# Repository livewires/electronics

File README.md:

# LiveWires Electronics Repo

Welcome to the LiveWires electronics repo. Eventually hopefully all the project information will be on here. For now it's just the new projects since this has been created.

Worksheets can be downloaded by finding the latest release (check the right hand bar on github) and downloading the worksheets.zip file

## Macro Pad

This is the LiveWires Macro Pad, an 8-key macro pad based on a Raspberry Pi Pico and cherry switches. It has up to 16 configurable pages of keys, and runs CircuitPython.

[Click here to find out more](macropad/README.md)

## Analogue Synthesiser

This is the LiveWires analogue synthesiser, a musical instrument with 5 octaves of output, a 1 octave keyboard, 8 control dials and entirely analogue processing of a digitally produced wave.

[Click here to find out more](synth/README.md)

## 3D LED Cube

The LiveWires LED cube, a 3x3x3 grid of LEDs with custom animations. 

[Click here to find out more](led-cube/README.md)

## Release Process

Create a draft release by going to `Releases > Draft a new release` in github.

Set the title accordingly, and change the "Tag" to create a new tag, vX.Y, where X.Y must be larger than the previous release. Describe the reason for doing the release in the description.

Download the worksheets.zip artifact from a build run with the desired changes, and upload them to the release. If no build has been performed in the last 90 days, you will need to manually trigger a new build. Go to the actions page, click on the action on the left hand side titled "Build LaTeX Documents" and then click the "Run Workflow" button

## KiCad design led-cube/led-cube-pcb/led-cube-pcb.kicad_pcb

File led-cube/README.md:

# LiveWires LED Cube

A 3x3x3 cube with completely programmable animations using the [animator](http://livewires.org.uk/led-cube)

## Own an LED cube? Start here!

Well done for building your LED cube! Here's where you can find all the information about it.

## How it works

The cube has 27 LEDs arranged in a 3×3×3 grid. Rather than wiring each LED individually, they share connections by layer — only one layer is switched on at a time, but they cycle through fast enough (~98 times per second) that all three appear lit at once.

This cycling is handled by the Pico's PIO hardware, which runs independently in the background so Python doesn't have to worry about the timing. Python's only job is to advance through the animation frames at the right speed and update which LEDs should be on.

Animations are loaded from `animations.json`. Each animation has a list of frames and a framerate. Pressing the button on GP16 skips to the next animation.

### Putting your own animations on

Use our [animation tool](http://livewires.org.uk/led-cube)! You can load the existing animations from the cube using the "Load JSON" button at the bottom. All you need to do is plug the pico in over USB and it'll appear as a removable drive. 

Once you're ready to try your animations on the cube, press "Download JSON" and move the `animations.json` file to the pico. Note, it must be named exactly that, if you've got several copies (e.g. `animations (1).json`) you'll have to rename it on the device. 

### Troubleshooting

That should be all you need. If you get stuck, feel free to get in touch with a leader, or post an issue here on github. 

If you've bricked your cube by changing something, don't worry, it should be easy to fix. Just download the contents of the "code" folder in github and copy it across to the device. 

## Setting up for the camp?

This should only need to be done by the leader running the sessions on the camp. This is what needs doing in advance:

* PCB needs ordering
* Components need kitting
* Pico needs soldering
* Pico needs initial software installing
* Jig needs making

#### PCB 

At the minute, this is a non-etch project. The PCB is ordered from JLCPCB or a similar service using the gerber files. These can be found in the version's output folder (e.g. [here](led-cube-pcb/releases/lw-led-cube_1.0/lw-led-cube_1.0_Gerbers.zip)).

These will take a few weeks to arrive so needs doing in plenty of time!

#### Components

Components list is in the BOM. For example, the revision 1 BOM can be found at [macropad-rev1/output/macropad-rev1-BOM.ods](led-cube-pcb/releases/lw-led-cube_1.0/full-project-bom_1.0.ods). 

#### Soldering the Pico

To save money, we're ordering the Pi Pico un-soldered. This means a leader will have to solder the two 20-pin headers to the Pico. They should protrude from the bottom of the Pico (i.e. the side with no components on), so the solder goes on the top of the board (i.e. the side _with_ the components on). 

#### Setting up the Pico

CircuitPython needs installing on the Pico, and then our code needs copying. The version used for development was 10.2.1, which is [copied into this repo](adafruit-circuitpython-raspberry_pi_pico-en_GB-10.2.1.uf2). 

You should now be able to copy the contents of the [code](code) folder onto the new CIRCUITPY drive. 

##### 1. Flash CircuitPython

Hold the **BOOTSEL** button on the Pico, plug it into USB, then release BOOTSEL.  
The Pico will appear as a USB drive called **RPI-RP2**.

Copy the firmware onto that drive:

```
adafruit-circuitpython-raspberry_pi_pico-en_GB-10.2.1.uf2  →  RPI-RP2
```

The Pico will reboot automatically and reappear as **CIRCUITPY**.

##### 2. Copy the code

Copy the contents of the `code/` folder to the root of the CIRCUITPY drive:

```
code/
├── code.py           →  CIRCUITPY/code.py
├── animations.json   →  CIRCUITPY/animations.json
└── lib/
    └── adafruit_pioasm.mpy  →  CIRCUITPY/lib/adafruit_pioasm.mpy
```

The Pico will run `code.py` automatically as soon as the files are in place.

#### Making a Jig

Soldering the pico headers to the PCB is much easier for the YP if they can physically join both 20-pin connectors together, the right distance apart. This can be done by attaching the connectors to a Pico before soldering them, but this risks breaking the Pico. So a jig can be made using header pins and a bit of veroboard. 

Use a Pico to copy the exact spacing of the pins. It should look something like this:

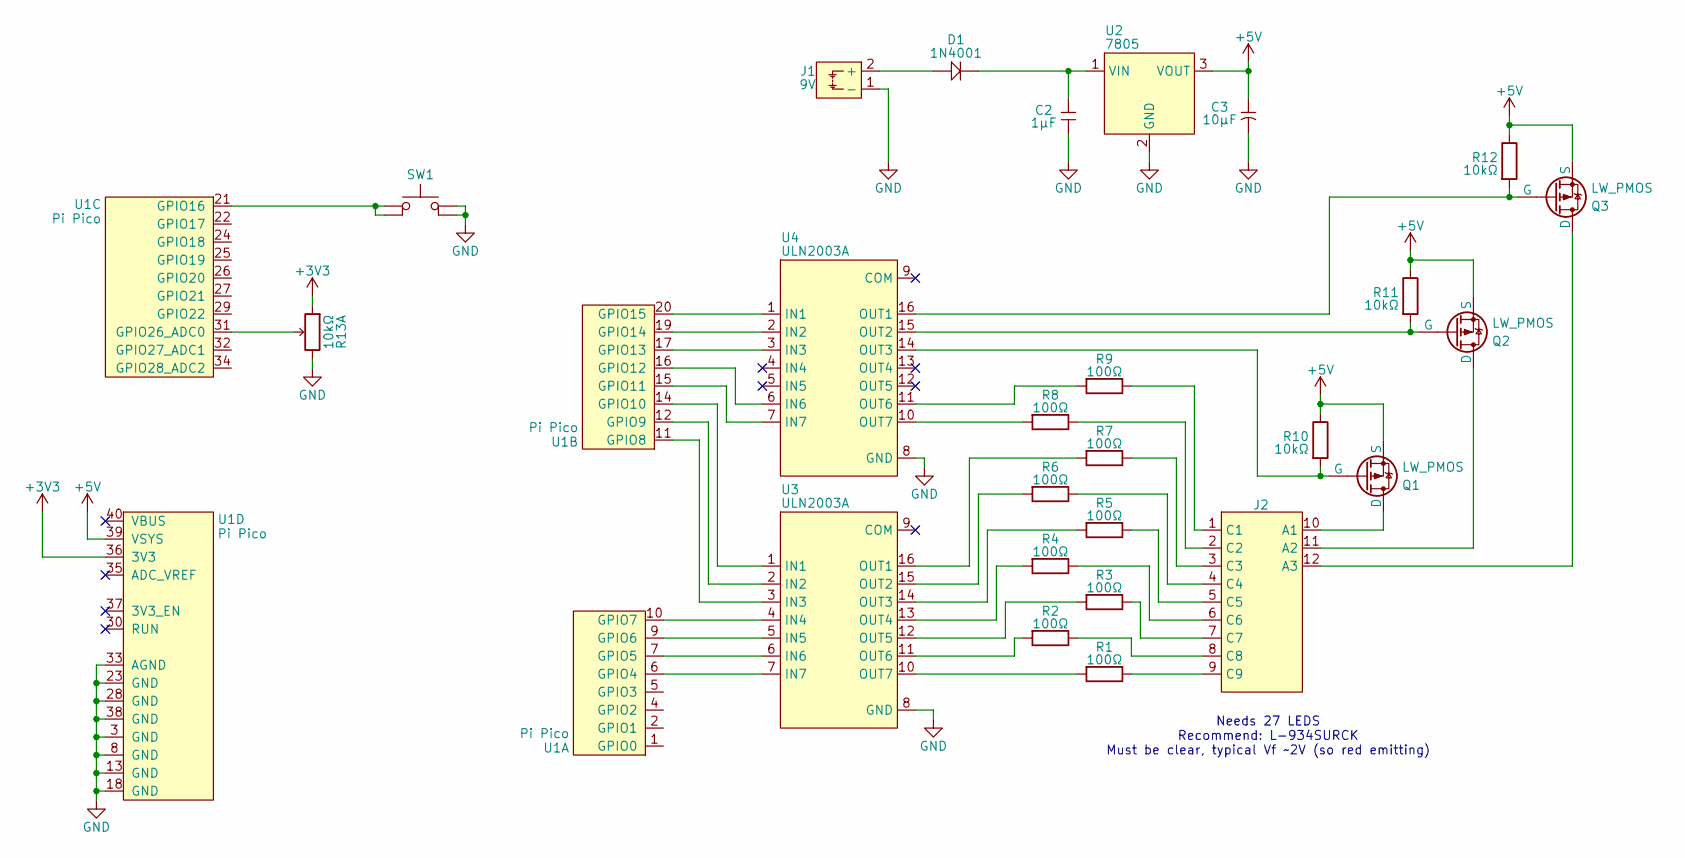
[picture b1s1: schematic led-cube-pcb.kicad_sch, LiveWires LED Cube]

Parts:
C2: 1µF; LW_CeramicCap_5.08mm; MPN TS170R1H105MSBFB0R
C3: 10µF; LW_CAP_Radial_D5.0mm_P2.00mm; MPN TS13DE1E100MSB030R
D1: 1N4001; LW_DIODE; MPN 1N4001
J1: 9V; LW_BATTERY_HOLDER; MPN 9V-I-Clip
J2: LED Cube; LW_LEDCUBE
Q1, Q2, Q3: LW_PMOS; LW_TO-92; MPN ZVP2110A
R1, R2, R3, R4, R5, R6, R7, R8, R9: 100Ω; LW_Res; MPN MF0W4FF1000
R10, R11, R12: 10kΩ; LW_Res; MPN MF0W4FF1002
R13: 10kΩ; PTV112-4420A; MPN PTV112-4420A-A103
SW1: LW_Tactile_Switch; LW_TACTILE_SW; MPN 783862
U1: Pi Pico; LW_RPi_Pico_SMD_TH; MPN SC0915
U2: 7805; TO-220-3_Vertical; MPN L7805
U3, U4: ULN2003A; DIP-16_W7.62mm_Socket; MPN ULN2003A

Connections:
+3V3: R13.2 (L), U1.36 (3V3)
+5V: C3.1, Q1.1 (S), Q2.1 (S), Q3.1 (S), R10.2, R11.2, R12.2, U1.39 (VSYS), U2.3 (VOUT)
GND: C2.1, C3.2, J1.1 (-), R13.6 (R), SW1.3, SW1.4, U1.3 (GND), U1.8 (GND), U1.13 (GND), U1.18 (GND), U1.23 (GND), U1.28 (GND), U1.33 (AGND), U1.38 (GND), U2.2 (GND), U3.8 (GND), U4.8 (GND)
unnamed: D1.A, J1.2 (+)
unnamed: J2.10 (A1), Q1.3 (D)
unnamed: J2.11 (A2), Q2.3 (D)
unnamed: J2.12 (A3), Q3.3 (D)
unnamed: J2.1 (C1), R9.2
unnamed: J2.2 (C2), R8.2
unnamed: J2.3 (C3), R7.2
unnamed: J2.4 (C4), R6.2
unnamed: J2.5 (C5), R5.2
unnamed: J2.6 (C6), R4.2
unnamed: J2.7 (C7), R3.2
unnamed: J2.8 (C8), R2.2
unnamed: J2.9 (C9), R1.2
unnamed: Q1.2 (G), R10.1, U4.14 (OUT3)
unnamed: Q2.2 (G), R11.1, U4.15 (OUT2)
unnamed: Q3.2 (G), R12.1, U4.16 (OUT1)
unnamed: R13.1 (C), U1.31 (GPIO26_ADC0)
unnamed: U1.6 (GPIO4), U3.7 (IN7)
unnamed: U1.7 (GPIO5), U3.6 (IN6)
unnamed: U1.9 (GPIO6), U3.5 (IN5)
unnamed: U1.10 (GPIO7), U3.4 (IN4)
unnamed: U1.11 (GPIO8), U3.3 (IN3)
unnamed: U1.12 (GPIO9), U3.2 (IN2)
unnamed: U1.14 (GPIO10), U3.1 (IN1)
unnamed: U1.15 (GPIO11), U4.7 (IN7)
unnamed: U1.16 (GPIO12), U4.6 (IN6)
unnamed: U1.17 (GPIO13), U4.3 (IN3)
unnamed: U1.19 (GPIO14), U4.2 (IN2)
unnamed: U1.20 (GPIO15), U4.1 (IN1)
unnamed: SW1.1, SW1.2, U1.21 (GPIO16)
unnamed: C2.2, D1.K, U2.1 (VIN)
unnamed: R7.1, U3.16 (OUT1)
unnamed: R6.1, U3.15 (OUT2)
unnamed: R5.1, U3.14 (OUT3)
unnamed: R4.1, U3.13 (OUT4)
unnamed: R3.1, U3.12 (OUT5)
unnamed: R2.1, U3.11 (OUT6)
unnamed: R1.1, U3.10 (OUT7)
unnamed: R9.1, U4.11 (OUT6)
unnamed: R8.1, U4.10 (OUT7)

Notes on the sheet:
Needs 27 LEDS Recommend: L-934SURCK Must be clear, typical Vf ~2V (so red emitting)

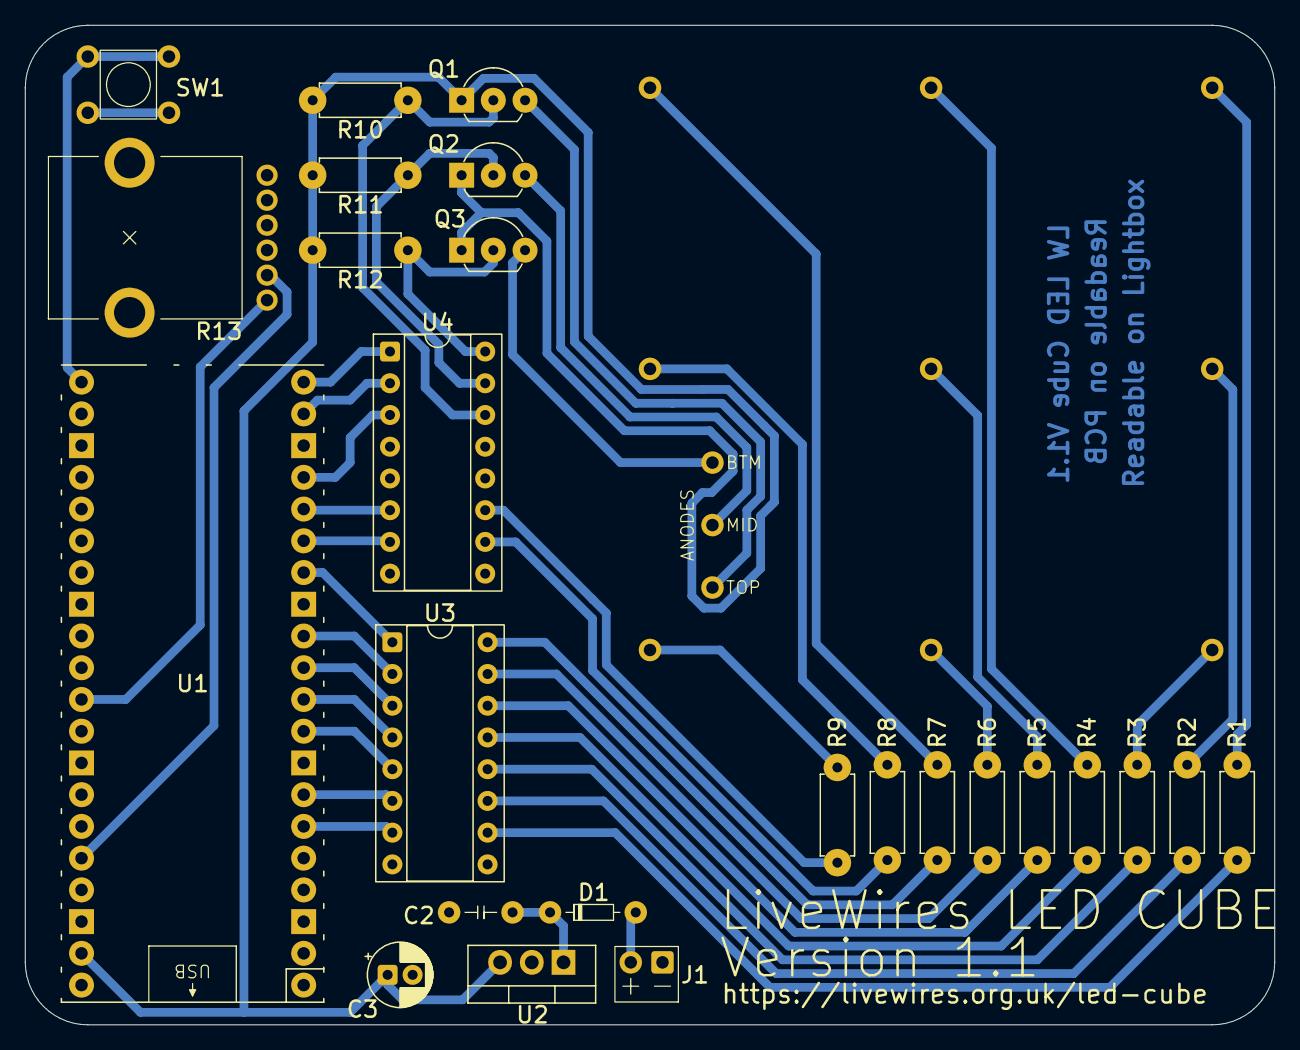
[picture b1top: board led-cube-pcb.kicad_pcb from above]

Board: 2 copper layers, 100.0 x 80.0 mm, 26 parts (0 on the bottom side), 43 nets.

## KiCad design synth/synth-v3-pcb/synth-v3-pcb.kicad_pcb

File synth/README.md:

# LiveWires Analogue Synthesiser

## Specification

 * Total range: 5 octaves (C1 to C6)
 * Keyboard: 1 octave capacitive touch keyboard
 * Wave generator: Sine wave
 * Low Frequency Oscillator (LFO) to control volume
 * Attack and Release envelopes
 * Overdrive for distortion
 * Low Pass Filter (LPF) with cutoff and resonance control
 * 3.5mm jack output for headphones

## Pictures

## How it works

13 capacitive touch keys (plus an additional two control buttons) are read by the pi pico. The pico generates a sine wave and outputs it using Pulse Width Modulation (PWM) to simulate an analogue output (since the pico doesn't come equipped with a DAC onboard). This signal is low-pass-filtered using a 2nd order RC filter, which makes it more closely approximate a sine wave.

An LFO generates a low-frequency (~0.05 - 5Hz) triangle wave. The Pico also outputs a digital signal that indicates whether a key is pressed, which is filtered by the Attack-Release (AR) circuitry. 

The voltage controlled amplifier (VCA) amplifies the sine wave by the control signal, which is the combination of the LFO and AR outputs.

The VCA output is then fed through the Low Pass Filter. 

## Setting up for the camp?

This should only need to be done by the leader running the sessions on the camp. This is what needs doing in advance:

* PCB needs ordering
* Components need kitting
* Pico needs soldering
* Pico needs software installing

#### PCB 

This is a non-etch project. The PCB is ordered from JLCPCB or a similar service using the gerber files. These can be found in the version's output folder (in [here](synth-v3-pcb/releases/)). Look for `*-gerbers.zip`. 

> [!IMPORTANT]
> These will take a few weeks to arrive so needs doing in plenty of time!

The JLCPCB ordering details are as follows:
* Basic Info
  * Base material: FR4
  * Layers: 2
  * Dimensions: [Automatic based on PCB gerbers]
  * Product type: Industrial/Consumer Electronics
* PCB Specification
  * Different Design: 1
  * Delivery Format: Single PCB
  * PCB Thicknes: 1.6mm
  * PCB Color: Black
  * Silkscreen: White
  * Material type: <doesn't matter, cheapest>
  * Surface finish: "LeadFree HASL" or "ENIG"
* High-Spec Options
  * Outer copper weight: 1oz
  * Via covering: Tented
  * Via plating method: Not specified
  * Min via hole size/diameter: 0.3mm <largest and therefore cheapest minimum at time of writing. Actual via diameter in board design is 0.35mm>
  
All other options set to cheapest option, usually defaults

### Components

Components list is in the BOM. For example, the revision 3.1 BOM can be found at [synth-v3-pcb/releases/lw-synth-v3.1/full-project-bom_rev_3.1.ods](synth-v3-pcb/releases/lw-synth-v3.1/full-project-bom_rev_3.1.ods). 

Knobs can be ordered for this project, but if available, 3D printed ones are easier and cheaper. The files for this can be found in `electronics/components/knobs`. If you are ordering some, be aware that some knobs you can order don't have the correct orientation of the ident in relation to the D of the potentiometer shaft. 

### Soldering the Pico

To save money, we're ordering the Pi Pico un-soldered. This means a leader will have to solder the two 20-pin headers to the Pico. They should protrude from the bottom of the Pico (i.e. the side with no components on), so the solder goes on the top of the board (i.e. the side _with_ the components on). 

#### Making a Jig

See the readme for the macropad project.

### Setting up the Pico's software

The software for the pico is written in C (not micropython, like the macropad). This means you simply need to copy [lw-synth.uf2](lw-synth.uf2) to the Pico's drive.

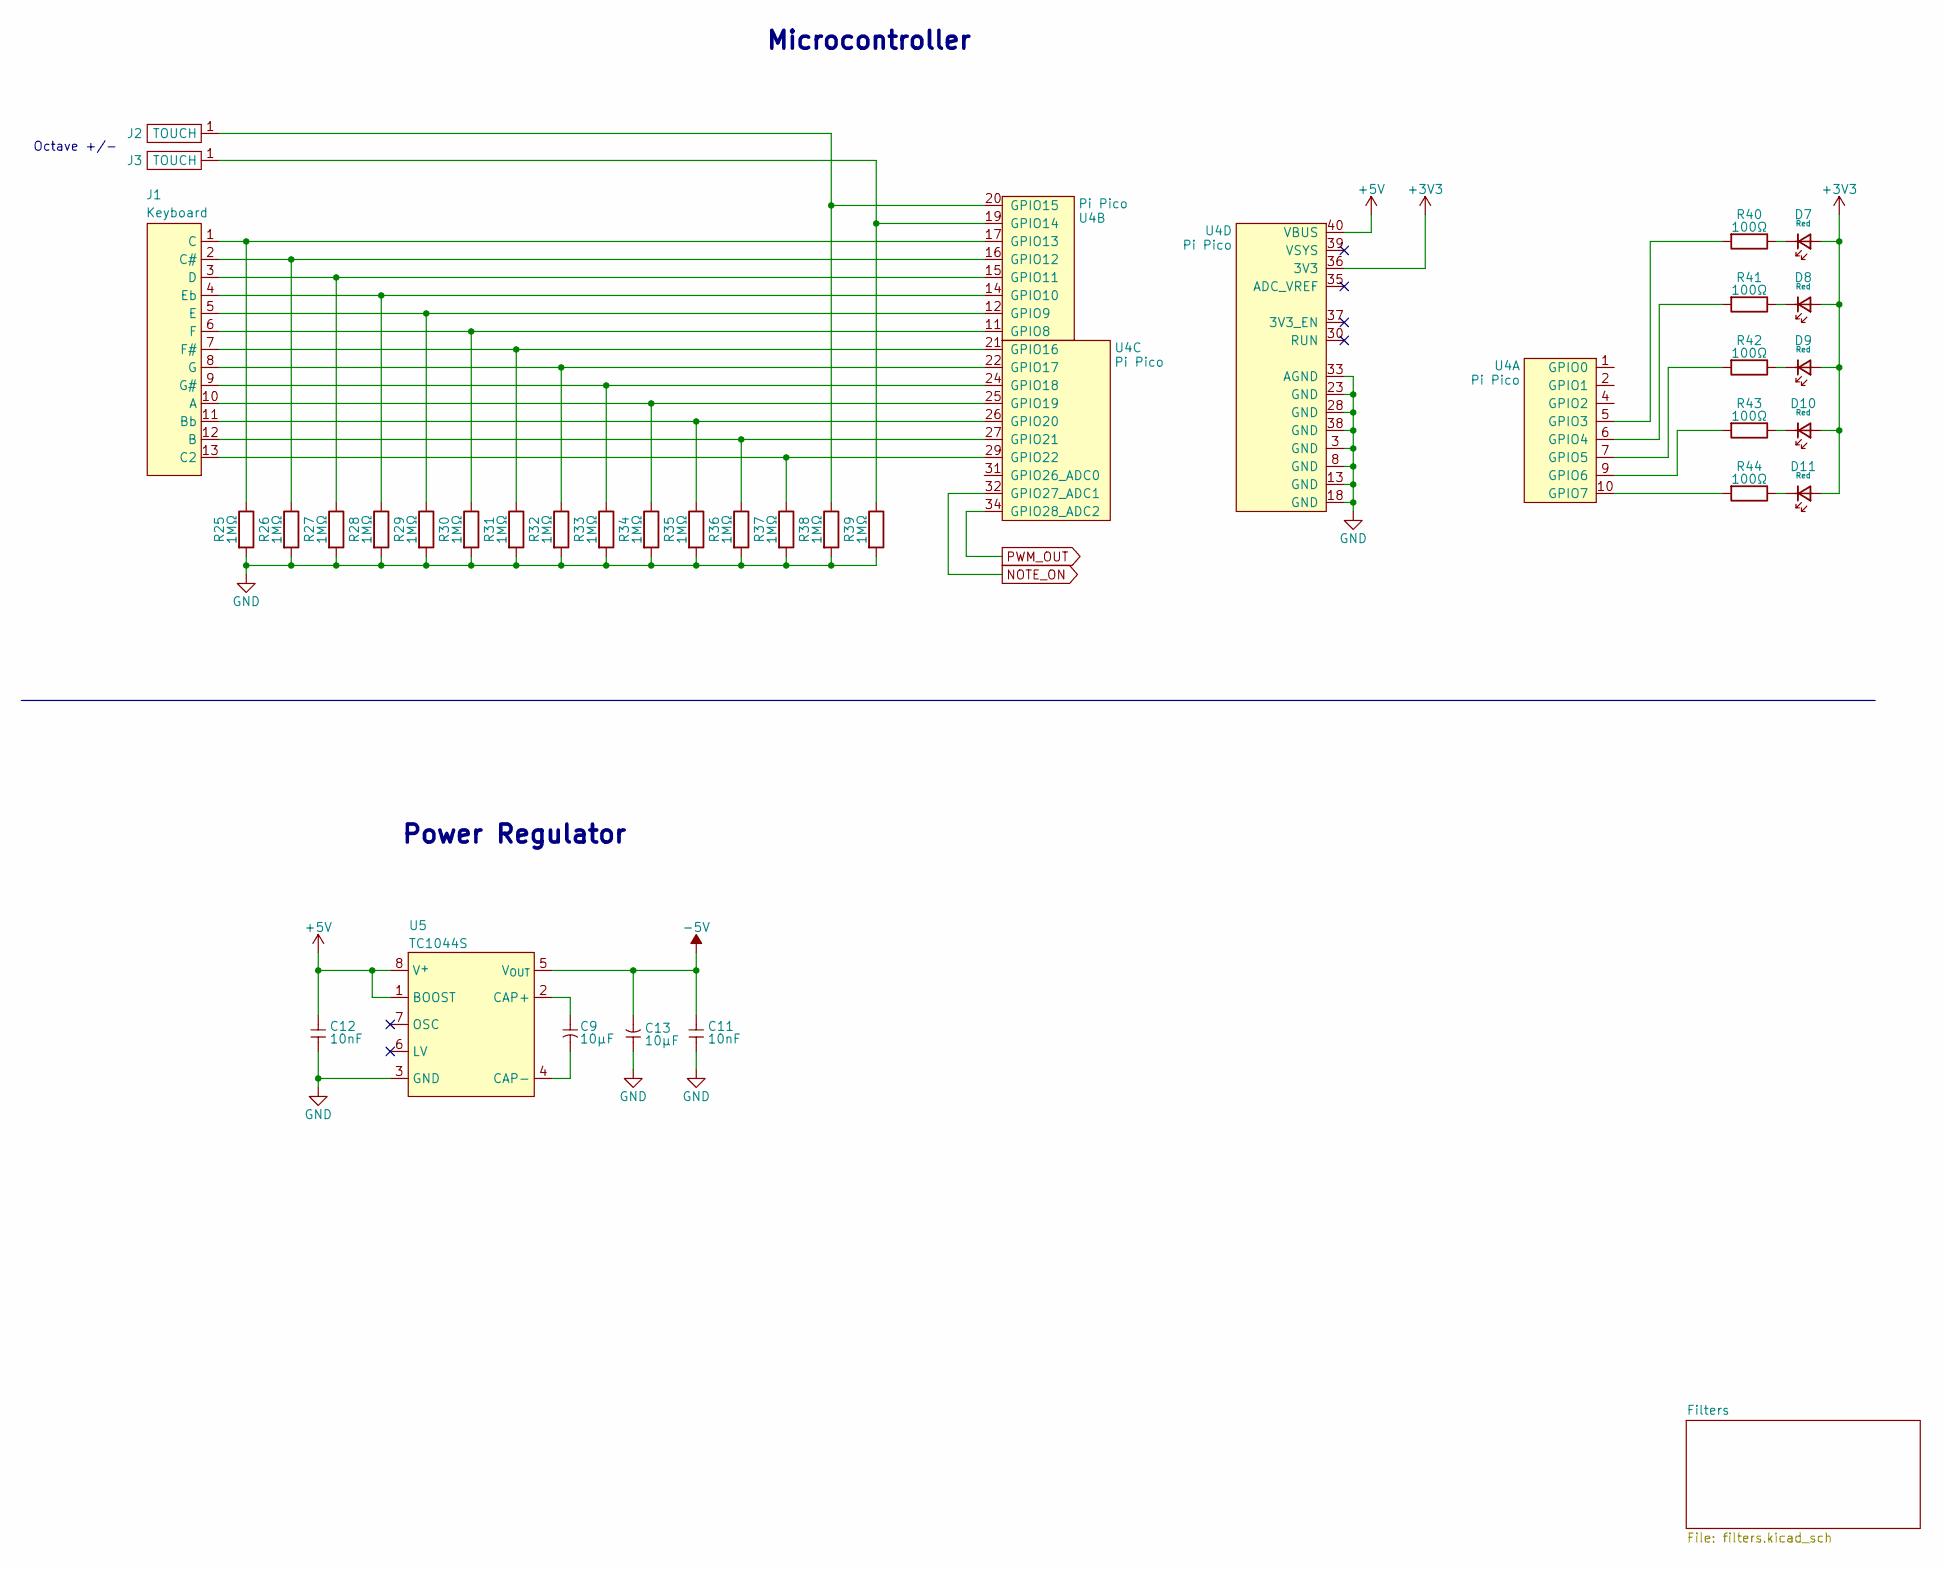
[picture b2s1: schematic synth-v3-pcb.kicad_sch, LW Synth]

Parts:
C9, C13: 10µF; LW_CAP_Radial_D5.0mm_P2.00mm; MPN TS13DE1E100MSB030R
C11, C12: 10nF; LW_CeramicCap_5.08mm; MPN TS170R1H103MSBFB0R
D7, D8, D9, D10, D11: Red; LW_LED_D5.0mm; MPN 1573708
J1: Keyboard; LW_PIANO
J2, J3: 15mm Touch; BASIC_TOUCH_PAD_15mm
R25, R26, R27, R28, R29, R30, R31, R32, R33, R34, R35, R36, R37, R38, R39: 1MΩ; LW_Res; MPN MF0W4FF1004
R40, R41, R42, R43, R44: 100Ω; LW_Res; MPN MF0W4FF1000
U4: Pi Pico; LW_RPi_Pico_SMD_TH; MPN SC0915
U5: TC1044S; LW_DIP8; MPN TC1044SCPA

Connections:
+3V3: D7.A, D8.A, D9.A, D10.A, D11.A, U4.36 (3V3)
+5V: C12.2, U4.40 (VBUS), U5.1 (BOOST), U5.8 (V^{+}); also elsewhere on the board
-5V: C11.2, C13.2, U5.5 (V_{OUT}); also elsewhere on the board
GND: C11.1, C12.1, C13.1, R25.1, R26.1, R27.1, R28.1, R29.1, R30.1, R31.1, R32.1, R33.1, R34.1, R35.1, R36.1, R37.1, R38.1, R39.1, U4.3 (GND), U4.8 (GND), U4.13 (GND), U4.18 (GND), U4.23 (GND), U4.28 (GND), U4.33 (AGND), U4.38 (GND), U5.3 (GND); also elsewhere on the board
NOTE_ON: U4.32 (GPIO27_ADC1); also elsewhere on the board
unnamed: D7.K, R40.2
unnamed: D8.K, R41.2
unnamed: D9.K, R42.2
unnamed: D10.K, R43.2
unnamed: D11.K, R44.2
unnamed: J1.10 (A), R34.2, U4.25 (GPIO19)
unnamed: J1.12 (B), R36.2, U4.27 (GPIO21)
unnamed: J1.11 (Bb), R35.2, U4.26 (GPIO20)
unnamed: J1.13 (C2), R37.2, U4.29 (GPIO22)
unnamed: J1.2 (C#), R26.2, U4.16 (GPIO12)
unnamed: J1.1 (C), R25.2, U4.17 (GPIO13)
unnamed: J1.3 (D), R27.2, U4.15 (GPIO11)
unnamed: J1.5 (E), R29.2, U4.12 (GPIO9)
unnamed: J1.4 (Eb), R28.2, U4.14 (GPIO10)
unnamed: J1.7 (F#), R31.2, U4.21 (GPIO16)
unnamed: J1.6 (F), R30.2, U4.11 (GPIO8)
unnamed: J1.9 (G#), R33.2, U4.24 (GPIO18)
unnamed: J1.8 (G), R32.2, U4.22 (GPIO17)
unnamed: J2.1 (TOUCH), R38.2, U4.20 (GPIO15)
unnamed: J3.1 (TOUCH), R39.2, U4.19 (GPIO14)
unnamed: R40.1, U4.5 (GPIO3)
unnamed: R41.1, U4.6 (GPIO4)
unnamed: R42.1, U4.7 (GPIO5)
unnamed: R43.1, U4.9 (GPIO6)
unnamed: R44.1, U4.10 (GPIO7)
unnamed: C9.1, U5.2 (CAP+)
unnamed: C9.2, U5.4 (CAP-)
PWM_OUT: U4.34 (GPIO28_ADC2); also elsewhere on the board

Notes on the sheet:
Power Regulator
Microcontroller
Octave +/-

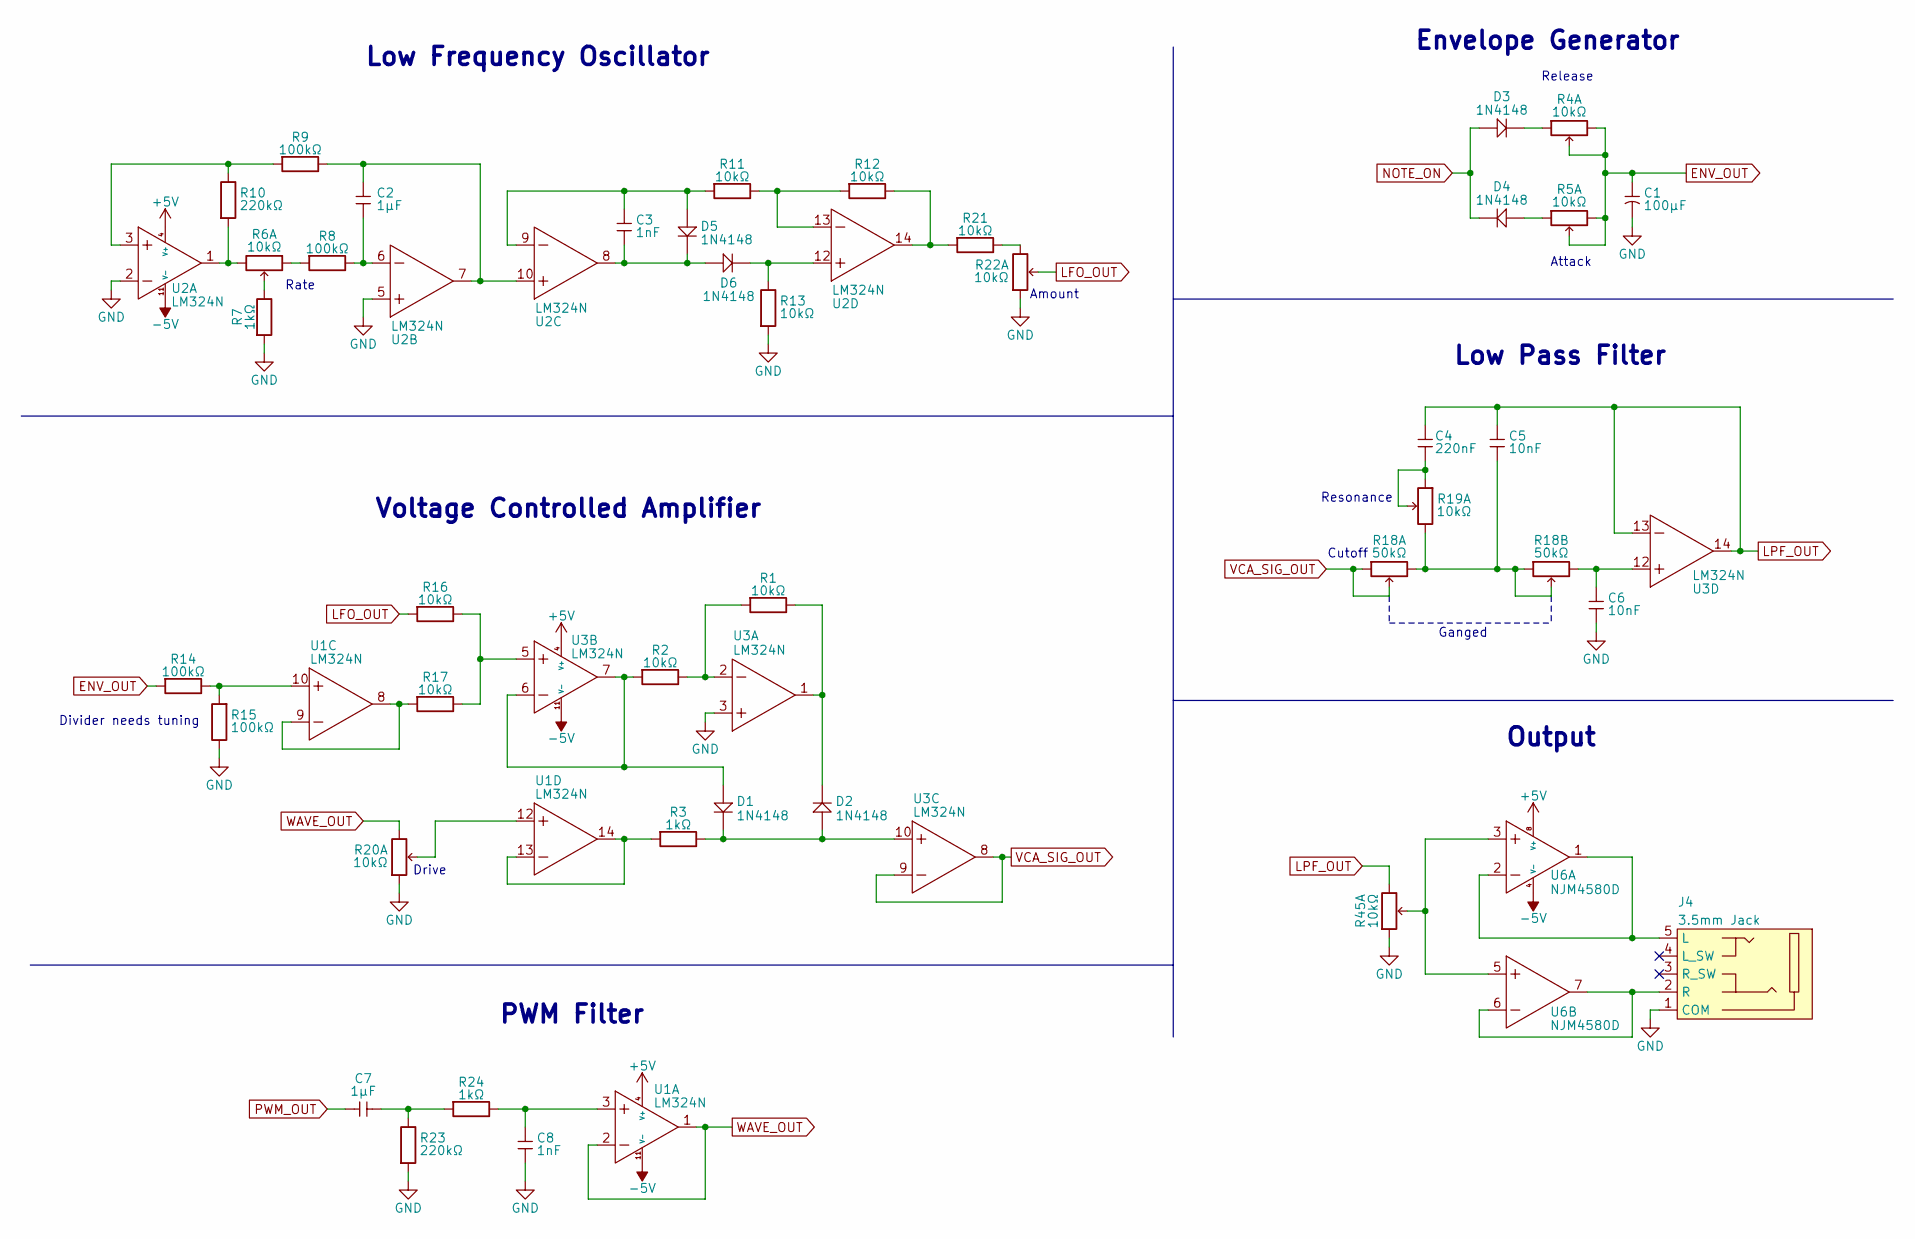
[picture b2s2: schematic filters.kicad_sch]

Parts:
C1: 100µF; LW_CAP_Radial_D6.3mm_P2.50mm; MPN TS13DE1V101MSB0A0R
C2, C7: 1µF; LW_CeramicCap_5.08mm; MPN TS170R1H105MSBFB0R
C3, C8: 1nF; LW_Cap_Disc; MPN TS170R2A102KSBBA0R
C4: 220nF; LW_CeramicCap_5.08mm; MPN TS170R1H224MSBFB0R
C5, C6: 10nF; LW_CeramicCap_5.08mm; MPN TS170R1H103MSBFB0R
D1, D2, D3, D4, D5, D6: 1N4148; LW_DIODE; MPN 1N4148-T26A
J4: 3.5mm Jack; LW_STEREO_JACK; MPN 20-0137
R1, R2, R11, R12, R13, R16, R17, R21: 10kΩ; LW_Res; MPN MF0W4FF1002
R3, R7, R24: 1kΩ; LW_Res; MPN MF0W4FF1001
R4, R5, R6, R19, R20, R22, R45: 10kΩ; PTV112-4420A; MPN PTV112-4420A-A103
R8, R9, R14, R15: 100kΩ; LW_Res; MPN MF0W4FF1003
R10, R23: 220kΩ; LW_Res; MPN MF0W4FF2203
R18: 50kΩ; PTV112-4420A; MPN PTV112-4420A-B503
U1, U2, U3: LM324N; LW_DIP14_Narrow; MPN LM324N
U6: NJM4580D; LW_DIP8; MPN NJM4580D

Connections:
+5V: U1.4 (V+), U2.4 (V+), U3.4 (V+), U6.8 (V+); also elsewhere on the board
-5V: U1.11 (V-), U2.11 (V-), U3.11 (V-), U6.4 (V-); also elsewhere on the board
ENV_OUT: C1.1, R4.1 (C), R4.6 (R), R5.1 (C), R5.6 (R), R14.1
GND: C1.2, C6.1, C8.1, J4.1 (COM), R7.1, R13.1, R15.2, R20.2 (L), R22.2 (L), R23.1, R45.2 (L), U2.2 (IN-), U2.5 (IN+), U3.3 (IN+); also elsewhere on the board
LFO_OUT: R16.1, R22.1 (C)
LPF_OUT: C4.2, C5.2, R45.6 (R), U3.13 (IN-), U3.14 (OUT)
NOTE_ON: D3.A, D4.K; also elsewhere on the board
unnamed: C7.2, R23.2, R24.1
unnamed: J4.5 (L), U6.1 (OUT), U6.2 (IN-)
unnamed: J4.2 (R), U6.6 (IN-), U6.7 (OUT)
unnamed: D3.K, R4.2 (L)
unnamed: D4.A, R5.2 (L)
unnamed: R6.1 (C), R7.2
unnamed: R6.2 (L), R8.1
unnamed: R6.6 (R), R10.1, U2.1 (OUT)
unnamed: C5.1, R18.3 (L), R18.4 (C), R18.6 (R), R19.6 (R)
unnamed: C6.2, R18.5 (R), U3.12 (IN+)
unnamed: C4.1, R19.1 (C), R19.2 (L)
unnamed: R20.1 (C), U1.12 (IN+)
unnamed: R21.2, R22.6 (R)
unnamed: R45.1 (C), U6.3 (IN+), U6.5 (IN+)
unnamed: C8.2, R24.2, U1.3 (IN+)
unnamed: R14.2, R15.1, U1.10 (IN+)
unnamed: R17.1, U1.8 (OUT), U1.9 (IN-)
unnamed: R3.1, U1.13 (IN-), U1.14 (OUT)
unnamed: R9.1, R10.2, U2.3 (IN+)
unnamed: C2.1, R8.2, U2.6 (IN-)
unnamed: C2.2, R9.2, U2.7 (OUT), U2.10 (IN+)
unnamed: C3.2, D5.A, R11.1, U2.9 (IN-)
unnamed: C3.1, D5.K, D6.A, U2.8 (OUT)
unnamed: D6.K, R13.2, U2.12 (IN+)
unnamed: R11.2, R12.1, U2.13 (IN-)
unnamed: R12.2, R21.1, U2.14 (OUT)
unnamed: R1.1, R2.2, U3.2 (IN-)
unnamed: D2.K, R1.2, U3.1 (OUT)
unnamed: R16.2, R17.2, U3.5 (IN+)
unnamed: D1.A, R2.1, U3.6 (IN-), U3.7 (OUT)
unnamed: D1.K, D2.A, R3.2, U3.10 (IN+)
PWM_OUT: C7.1; also elsewhere on the board
VCA_SIG_OUT: R18.1 (C), R18.2 (L), U3.8 (OUT), U3.9 (IN-)
WAVE_OUT: R20.6 (R), U1.1 (OUT), U1.2 (IN-)

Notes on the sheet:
Cutoff
Output
PWM Filter
Rate
Ganged
Low Frequency Oscillator
Resonance
Envelope Generator
Drive
Divider needs tuning
Amount
Low Pass Filter
Attack
Voltage Controlled Amplifier
Release

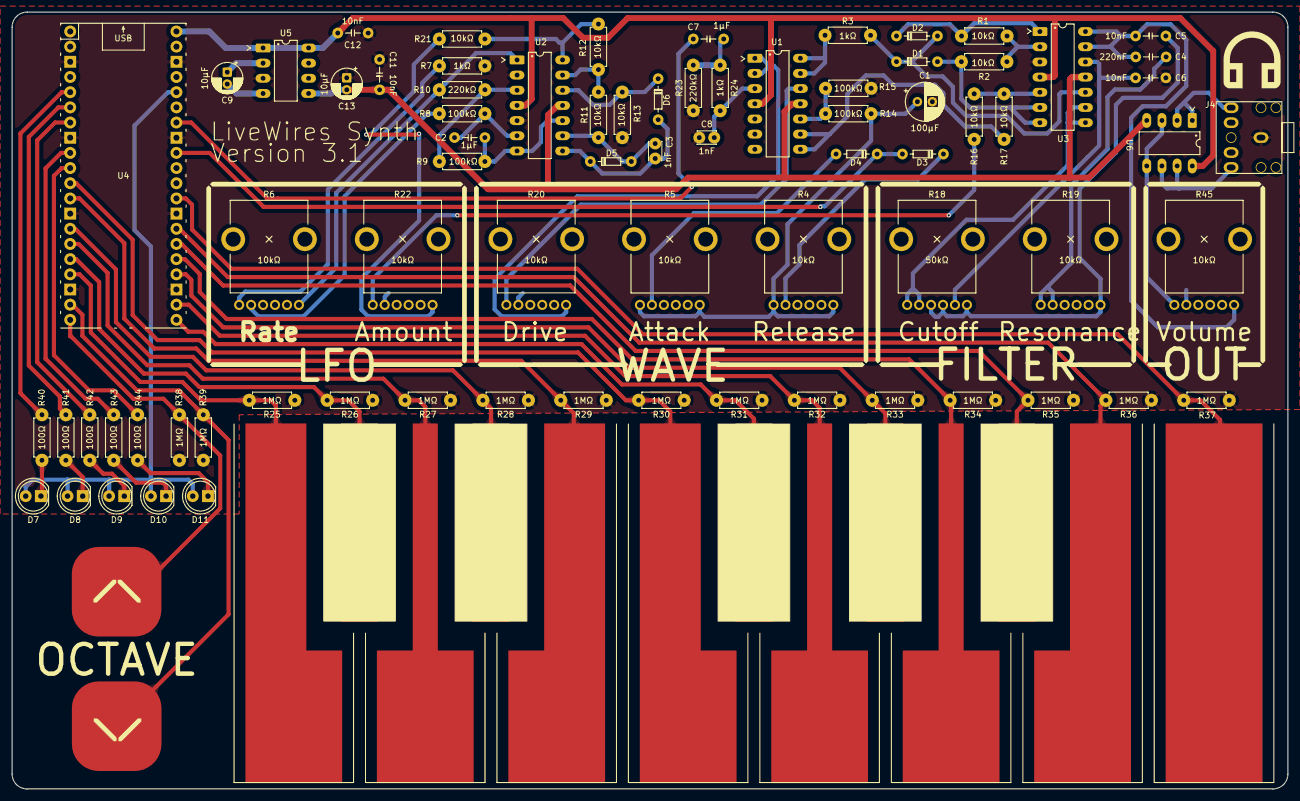
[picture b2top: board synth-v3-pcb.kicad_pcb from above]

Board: 2 copper layers, 213.5 x 130.0 mm, 78 parts (0 on the bottom side), 69 nets.

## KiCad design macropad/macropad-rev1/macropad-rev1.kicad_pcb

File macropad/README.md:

# LiveWires Macro Pad

An 8-key keyboard where each key can be programmed to do whatever you like. It's got up to 16 pages of macros
available, and is perfect for game button combos and productivity. 

## Own a macro pad? Start here!

Well done for building your macro pad! Here's where you can find all the information you need to start programming it yourself.

### How it works

The macro pad runs on a Raspberry Pi Pico. If you plug in the macro pad to a computer, it should do two things. Firstly, it'll act as the macro pad it's supposed to! Secondly, it should also act as a tiny memory stick, creating a new drive on your computer that you can browse the files on.

This contains two files - code.py and keys.py - plus a couple of folders.

Unless you're a Python wizard, we recommend you don't touch the folders, or code.py. These are what makes it all work as it should and you risk breaking things/

However, keys.py is where you can tell the macro pad which buttons do what. So this is the one to edit. You should be able to open it in your favourite text editor, make changes, save them and then unplug and plug back in the macro pad. However there's an easier way...

### Using Thonny

This isn't strictly required, but it is highly recommended. The best software we've found to edit the macro pad code is called Thonny. You should be able to download and install it from here: https://thonny.org/

Once installed, it should have a button in the bottom right corner that you can click to choose the option that mentions Circuit Python. On a Windows machine it probably says something like "CircuitPython (generic)  **·** COM3". Click that one.

Once you've done that, you can press File -> Open, and open the keys.py file that's on the device. 

Thonny will highlight the different bits of the code in different colours, which should help you understand the changes you want to make. 

Once you've made the changes to the file, press save. To run the new code immediately, you should just be able to press the red "stop" sign followed by the green "play" sign in the top bar of the Thonny window.

### Troubleshooting

That should be all you need. If you get stuck, feel free to get in touch with a leader, or post an issue here on github. 

If you've bricked your macropad by changing something, don't worry, it should be easy to fix. Just download the contents of the "code" folder in github and copy it across to the device. 

## Setting up for the camp?

This should only need to be done by the leader running the sessions on the camp. This is what needs doing in advance:

* PCB needs ordering
* Components need kitting
* Pico needs soldering
* Pico needs initial software installing
* Jig needs making

#### PCB 

At the minute, this is a non-etch project. The PCB is ordered from JLCPCB or a similar service using the gerber files. These can be found in the version's output folder (e.g. [here](macropad-rev1/output/macropad-rev1.zip)).

These will take a few weeks to arrive so needs doing in plenty of time!

#### Components

Components list is in the BOM. For example, the revision 1 BOM can be found at [macropad-rev1/output/macropad-rev1-BOM.ods](macropad-rev1/output/macropad-rev1-BOM.ods). 

The key switches can be ordered from a variety of places. For quick UK stock, mechboards are good, and the [gateron switches](https://mechboards.co.uk/collections/switches/products/gateron-blue?variant=41710358528205) are sensibly priced. In general the blue switches will give the clickiest feedback. For bulk numbers, keychron seems cheap, but it's coming from China so may take a while. 

The key caps are from AliExpress. They will also take a while to arrive. 

#### Soldering the Pico

To save money, we're ordering the Pi Pico un-soldered. This means a leader will have to solder the two 20-pin headers to the Pico. They should protrude from the bottom of the Pico (i.e. the side with no components on), so the solder goes on the top of the board (i.e. the side _with_ the components on). 

#### Setting up the Pico

CircuitPython needs installing on the Pico, and then our code needs copying. 

Detailed instructions for installing CircuitPython on the Pico can be found [here](https://learn.adafruit.com/getting-started-with-raspberry-pi-pico-circuitpython/circuitpython). The version used for development was 9.0.4, which is [copied into this repo](adafruit-circuitpython-raspberry_pi_pico-en_GB-9.0.4.uf2). To summarise in case of a dead link:
* While holding the BOOTSEL button on the pico down, plug it in to a computer using the USB cable
* Copy the CircuitPython uf2 file onto the RPI-RP2 drive that appears
* The RPI-RP2 drive should disappear and a CIRCUITPY drive should appear. 

You should now be able to copy the contents of the [code](code) folder onto the new CIRCUITPY drive. 

#### Making a Jig

Soldering the pico headers to the PCB is much easier for the YP if they can physically join both 20-pin connectors together, the right distance apart. This can be done by attaching the connectors to a Pico before soldering them, but this risks breaking the Pico. So a jig can be made using header pins and a bit of veroboard. 

Use a Pico to copy the exact spacing of the pins. It should look something like this:

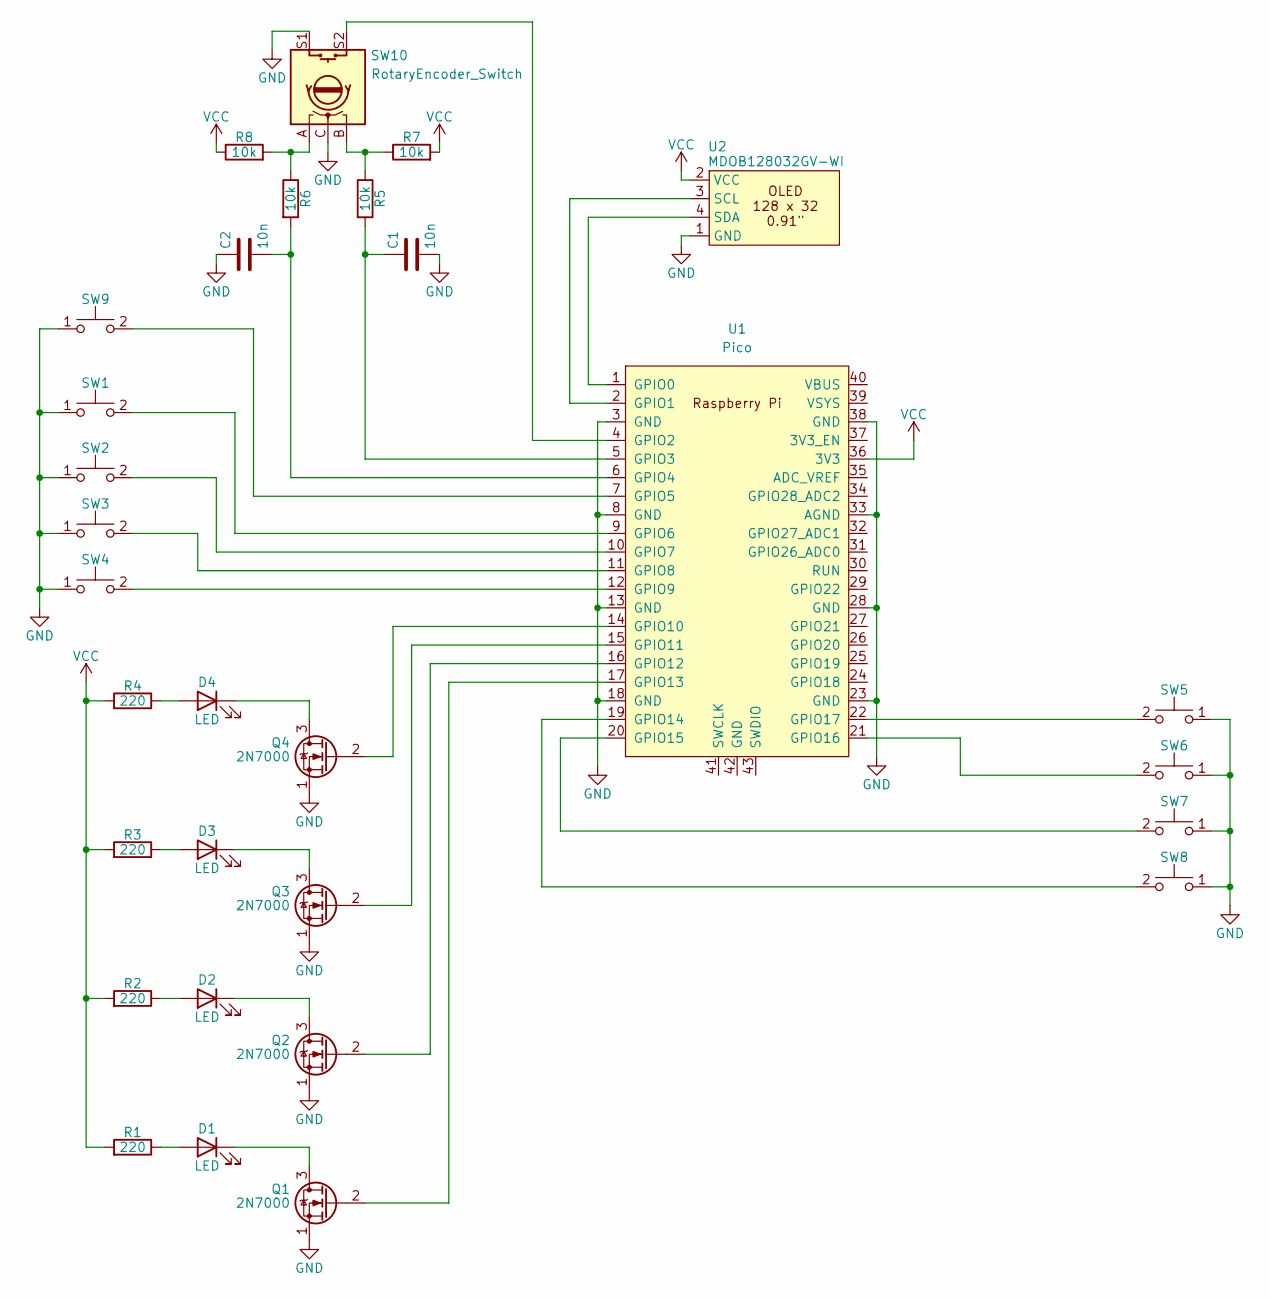
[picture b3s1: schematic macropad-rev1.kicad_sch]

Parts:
C1, C2: 10n; LW_Cap_Disc
D1, D2, D3, D4: LED; LW_LED_D5.0mm; MPN WP7113ID
Q1, Q2, Q3, Q4: 2N7000; LW_TO-92; MPN 2N7000
R1, R2, R3, R4: 220; LW_Res
R5, R6, R7, R8: 10k; LW_Res
SW1, SW2, SW3, SW4, SW5, SW6, SW7, SW8, SW9: LW_CherrySwitch; MPN Blue switch
SW10: RotaryEncoder_Switch; LW_RotaryEncoder_Bourns_Vertical_PEC12R-3x17F-Sxxxx; MPN PEC12R-4215F-S0024
U1: Pico; LW_RPi_Pico_SMD_TH; MPN Pi Pico
U2: MDOB128032GV-WI; LW_MIDAS_OLED_128x32_0.91in; MPN MDOB128032GV-WI

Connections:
GND: C1.2, C2.1, Q1.1 (S), Q2.1 (S), Q3.1 (S), Q4.1 (S), SW1.1, SW2.1, SW3.1, SW4.1, SW5.1, SW6.1, SW7.1, SW8.1, SW9.1, SW10.C, SW10.S1, U1.3 (GND), U1.8 (GND), U1.13 (GND), U1.18 (GND), U1.23 (GND), U1.28 (GND), U1.33 (AGND), U1.38 (GND), U2.1 (GND)
unnamed: D1.2 (A), R1.1
unnamed: D1.1 (K), Q1.3 (D)
unnamed: D2.2 (A), R2.1
unnamed: D2.1 (K), Q2.3 (D)
unnamed: D3.2 (A), R3.1
unnamed: D3.1 (K), Q3.3 (D)
unnamed: D4.2 (A), R4.1
unnamed: D4.1 (K), Q4.3 (D)
unnamed: Q1.2 (G), U1.17 (GPIO13)
unnamed: Q2.2 (G), U1.16 (GPIO12)
unnamed: Q3.2 (G), U1.15 (GPIO11)
unnamed: Q4.2 (G), U1.14 (GPIO10)
unnamed: R5.1, R7.1, SW10.B
unnamed: R6.1, R8.2, SW10.A
unnamed: U1.1 (GPIO0), U2.4 (SDA)
unnamed: U1.2 (GPIO1), U2.3 (SCL)
unnamed: SW10.S2, U1.4 (GPIO2)
unnamed: C1.1, R5.2, U1.5 (GPIO3)
unnamed: C2.2, R6.2, U1.6 (GPIO4)
unnamed: SW9.2, U1.7 (GPIO5)
unnamed: SW1.2, U1.9 (GPIO6)
unnamed: SW2.2, U1.10 (GPIO7)
unnamed: SW3.2, U1.11 (GPIO8)
unnamed: SW4.2, U1.12 (GPIO9)
unnamed: SW8.2, U1.19 (GPIO14)
unnamed: SW7.2, U1.20 (GPIO15)
unnamed: SW6.2, U1.21 (GPIO16)
unnamed: SW5.2, U1.22 (GPIO17)
VCC: R1.2, R2.2, R3.2, R4.2, R7.2, R8.1, U1.36 (3V3), U2.2 (VCC)

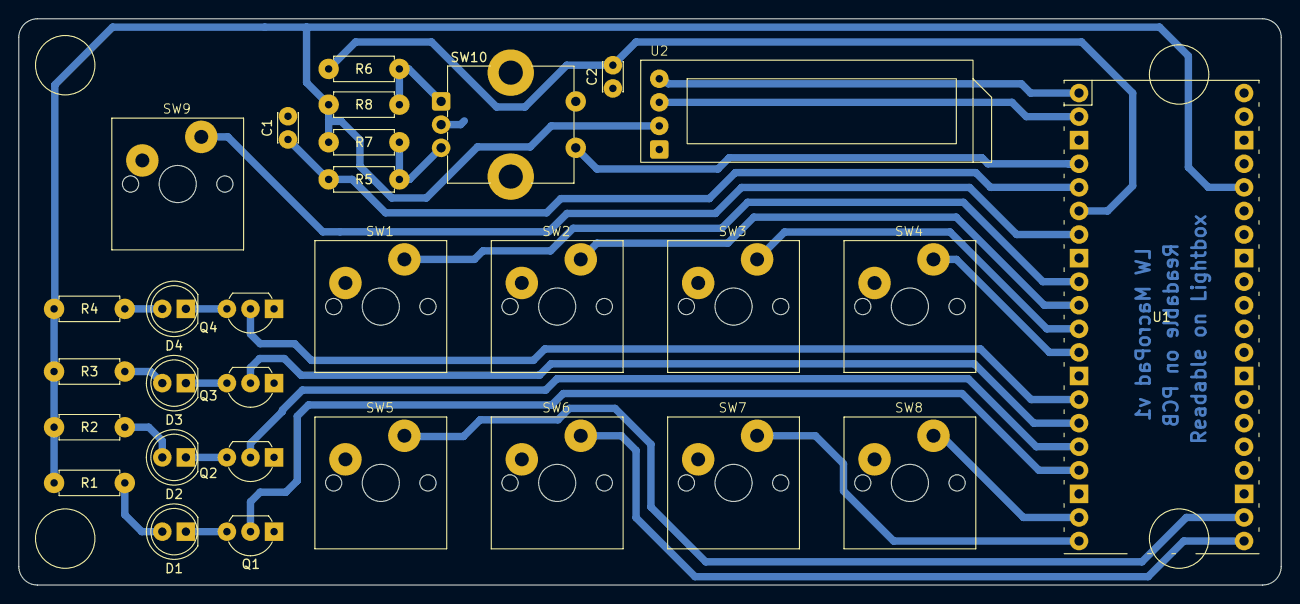
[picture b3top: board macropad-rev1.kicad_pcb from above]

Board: 2 copper layers, 136.0 x 61.0 mm, 30 parts (0 on the bottom side), 30 nets.

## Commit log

2024-04-20 Added first attempt at releasing macro pad
2024-04-21 Now using SVG and drill marks
2024-04-21 Found the better SVG output with small drill marks
2024-05-16 Working PCB
2024-05-16 Added some code
2024-05-16 Got most functionality working
2024-05-17 Documentation and robustness!
2024-05-17 Fixed encoder bug
2024-05-18 Added a lot of clarity post testing with Eliza
2024-05-18 Added READMEs
2024-05-18 Added image
2024-05-25 Added worksheet
2024-05-25 Added pipeline attempt
2024-05-25 Pipeline work
2024-05-25 Attempted change
2024-05-25 Attempt 2
2024-05-25 attempt 3
2024-05-26 attempt 4
2024-05-26 attempt 5
2024-05-26 attempt 6
2024-05-26 attempt 7
2024-05-26 attempt 8
2024-05-26 attempt 9
2024-05-27 New action
2024-05-27 changed permissions
2024-05-27 attempt 2.1
2024-05-27 attempt 2.2
2024-05-27 Tidying up
2024-05-27 PR test
2024-06-17 Removed etch from worksheet
2024-06-17 Added macro pad documentation for team
2024-06-17 Spelling fixes
2025-07-07 Added workflow dispatch line to workflow
2026-01-06 Initial PCB dev
2026-01-06 Released Synth V3.0
2026-01-22 Added glide feature
2026-01-26 Tidied code
2026-01-26 Released PCB v3.1 and added knobs
2026-01-26 Added README
2026-02-07 Added synth worksheet
2026-02-07 Updated build script
2026-02-07 Added release process to README
2026-04-16 Added first attempt at LED cube PCB
2026-05-15 Added initial LED cube code
2026-05-16 Added circuit python code options
2026-05-16 Made README and added all ancillary files
2026-05-16 Added web page animator
2026-05-16 Added worksheets and other fixes
2026-05-16 Added website build script
2026-05-16 Documentation updates
2026-05-18 Released v1.1 of the LED cube PCB, with better LED spacing and some convenience features
2026-05-19 Added LED help jig
2026-05-19 Added LED construction diagrams to worksheet
2026-05-19 Added photos to README
2026-06-20 Updated jig
2026-06-21 Fixed worksheets
2026-06-21 Removed accidentally committed files
